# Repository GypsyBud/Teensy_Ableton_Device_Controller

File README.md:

# Teensy_Ableton_Device_Controller
A small, cheap midi controller with instant mapping for devices in Ableton

Based on the Teensy LC micro controller. 

WORK IN PROGRESS.

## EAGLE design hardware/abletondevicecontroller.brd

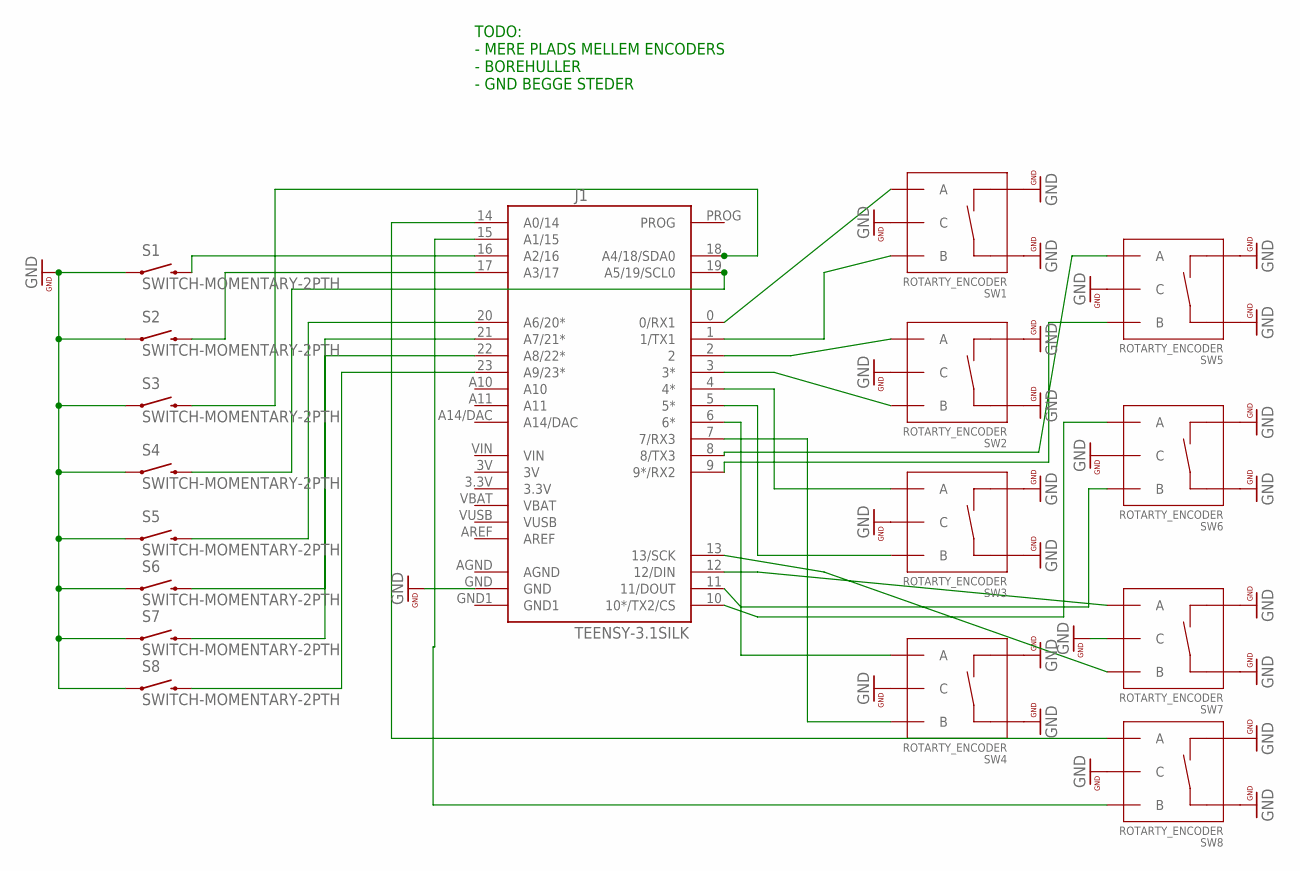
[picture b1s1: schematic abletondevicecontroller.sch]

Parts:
J1: TEENSY-3.1SILK; TEENSY-3.1
S1, S2, S3, S4, S5, S6, S7, S8: SWITCH-MOMENTARY-2PTH; TACTILE-PTH
SW1, SW2, SW3, SW4, SW5, SW6, SW7, SW8: ROTARTY_ENCODER; ROTARY_ENC_PLAIN

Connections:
GND: J1.GND, S1.1, S2.1, S3.1, S4.1, S5.1, S6.1, S7.1, S8.1, SW1.C, SW1.SW+, SW1.SW-, SW2.C, SW2.SW+, SW2.SW-, SW3.C, SW3.SW+, SW3.SW-, SW4.C, SW4.SW+, SW4.SW-, SW5.C, SW5.SW+, SW5.SW-, SW6.C, SW6.SW+, SW6.SW-, SW7.C, SW7.SW+, SW7.SW-, SW8.C, SW8.SW+, SW8.SW-
unnamed: J1.8 (8/TX3), SW5.A
unnamed: J1.9 (9*/RX2), SW5.B
unnamed: J1.10 (10*/TX2/CS), SW6.A
unnamed: J1.0 (0/RX1), SW1.A
unnamed: J1.1 (1/TX1), SW1.B
unnamed: J1.2, SW2.A
unnamed: J1.3 (3*), SW2.B
unnamed: J1.4 (4*), SW3.A
unnamed: J1.5 (5*), SW3.B
unnamed: J1.6 (6*), SW4.A
unnamed: J1.7 (7/RX3), SW4.B
unnamed: J1.11 (11/DOUT), SW6.B
unnamed: J1.12 (12/DIN), SW7.A
unnamed: J1.13 (13/SCK), SW7.B
unnamed: J1.14 (A0/14), SW8.A
unnamed: J1.15 (A1/15), SW8.B
unnamed: J1.16 (A2/16), S1.3 (2)
unnamed: J1.17 (A3/17), S2.3 (2)
unnamed: J1.20 (A6/20*), S5.3 (2)
unnamed: J1.19 (A5/19/SCL0), S4.3 (2)
unnamed: J1.21 (A7/21*), S6.3 (2)
unnamed: J1.22 (A8/22*), S7.3 (2)
unnamed: J1.23 (A9/23*), S8.3 (2)
unnamed: J1.18 (A4/18/SDA0), S3.3 (2)

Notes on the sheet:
TODO: - MERE PLADS MELLEM ENCODERS - BOREHULLER - GND BEGGE STEDER

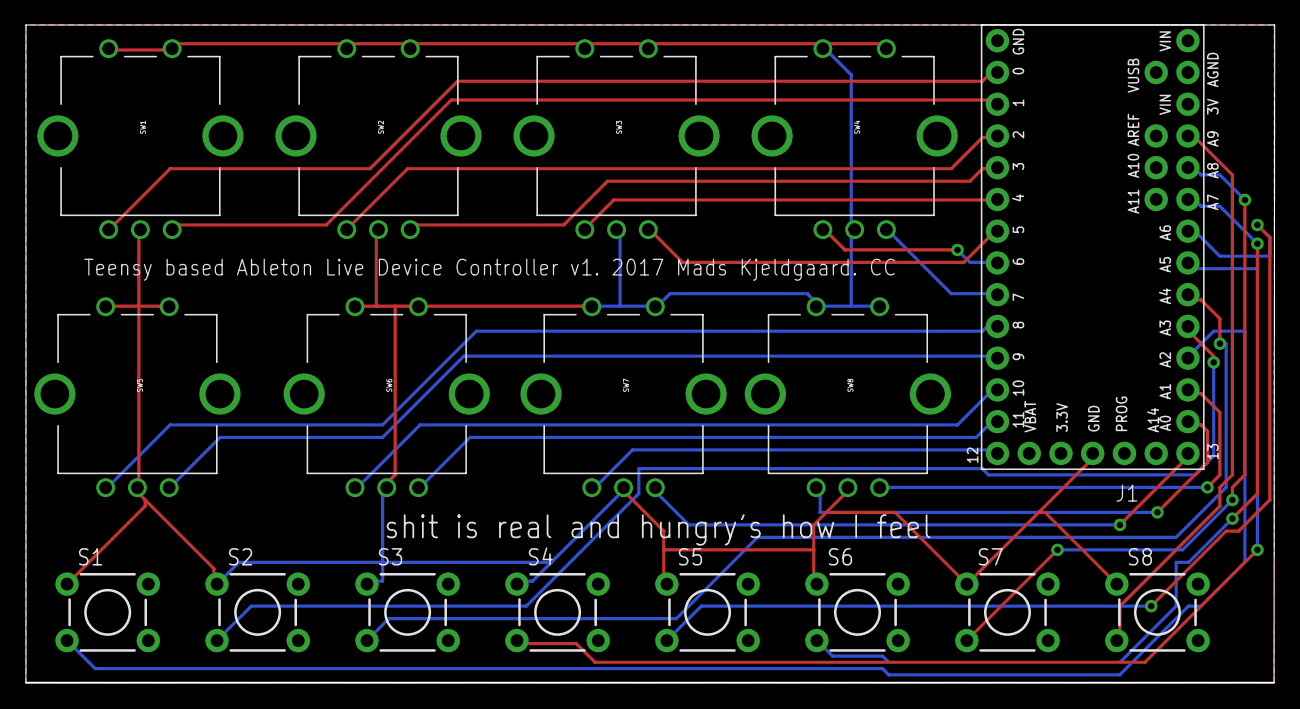
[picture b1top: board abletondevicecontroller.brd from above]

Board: 2 copper layers, 99.9 x 52.6 mm, 17 parts (0 on the bottom side), 25 nets.

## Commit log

2018-03-12 first commit
    first commit

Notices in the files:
parts and their libraries:
SparkFun-Boards: Licensing: Creative Commons ShareAlike 4.0 International - https://creativecommons.org/licenses/by-sa/4.0
PatternAgents-Beautify: License : http://creativecommons.org/licenses/by-sa/3.0
(Creative Commons 3.0)
